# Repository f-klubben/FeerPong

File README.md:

# FeerPong
F-klubbens overengineered og goldplated beerpong table!

For quite a while, two beautifully painted tables have been sitting in the dark corners of jægerstuen, ready to be turned into the nerdiest (and therefore also, coolest) beer pong tables known to man. This repository has therefore been created to conquer this stalemate and bring the dream to life. Currently, it is a bit empty in here, but in the future, we will collect everything relating to the FeerPong table in here. This will include, but not limited to, 2D files for the laser cutter that will engrave the table (already [here](PhysicalDesign/2DLogoLaserCutting), whoop!), code to the ontable-hardware and, of course, documentation for it all.

## FeerPong ideas:
- F-klubbens logo encompassing the beers ingraved into the tables via laser cutting
  - See [the 2D logo laser cutting files](PhysicalDesign/2DLogoLaserCutting)
- Diodes, sensors and ontable-hardware that can be used for various extensions of the traditional beer pong, truly bringing forth the era of FeerPong
  - Protocol ideas: (You are welcome to add more!)
    - Under_Score_Protocol
      - All active cups (cups on the table that has not yet been consumed) light up 
    - Holy_Grail_Protocol:
      - Randomly an active cup will light up for a set time. If that cup is hit the team owning the cup, recieve a penalty (drink an extra beer/shot, they also have to drink adjecent cups, End_Case_Protocol/Recursive_Protocol starts for them etc.)
    - Counter_Attack_Protocol:
      - When a cup is taken away (because the opposite team hit it) one or more cups on the opposite side light up for a short time. If the team downs the beer and then hit one of the cups, the oppsite team recieves a penalty (drink an extra beer/shot, they also have to drink adjecent cups, End_Case_Protocol/Recursive_Protocol starts for them etc.)
    - End_Case_Protocol/Recursive_Protocol:
      - When a cup is taken away (because the opposite team hit it) a timer starts. When the timer runs out a cup light up and if the team  haven't downed their beer before that, they have to drink that beer too, starting a new timer (this continues until you down a beer before the timer runs out or loose the game). The timer could be customisable 
  - Crazy new ideas: (Again, add more!)
    - Account creation and cross-game score keeping
    - App/web-app integration for game control, account management etc.

(You are also welcome to correct any spelling mistakes you find)

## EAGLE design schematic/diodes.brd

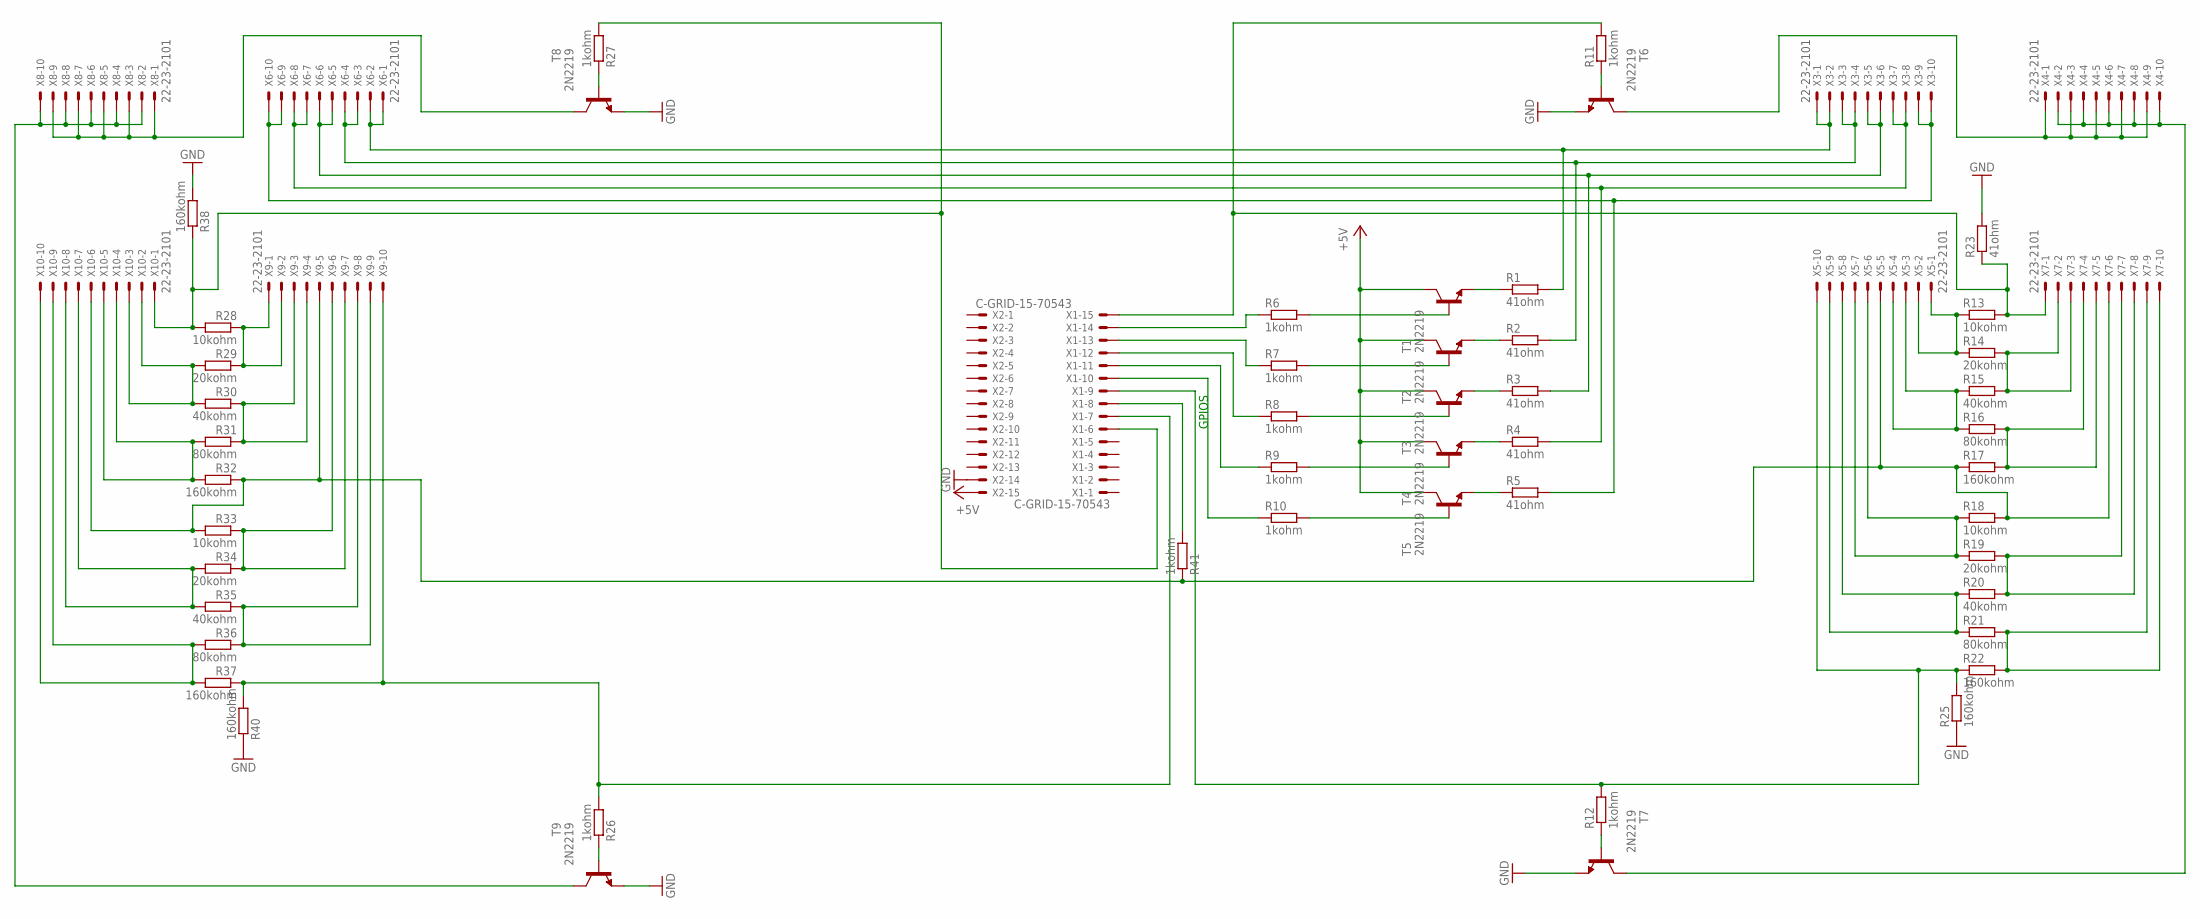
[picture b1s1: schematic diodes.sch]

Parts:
R1, R2, R3, R4, R5, R23: 41ohm; 0207/10
R6, R7, R8, R9, R10, R11, R12, R26, R27, R41: 1kohm; 0207/10
R13, R18, R28, R33: 10kohm; 0207/10
R14, R19, R29, R34: 20kohm; 0207/10
R15, R20, R30, R35: 40kohm; 0207/10
R16, R21, R31, R36: 80kohm; 0207/10
R17, R22, R25, R32, R37, R38, R40: 160kohm; 0207/10
T1, T2, T3, T4, T5, T6, T7, T8, T9: 2N2219; TO5
X1, X2: C-GRID-15-70543; 70543-15
X3, X4, X5, X6, X7, X8, X9, X10: 22-23-2101

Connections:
+5V: T1.3 (C), T2.3 (C), T3.3 (C), T4.3 (C), T5.3 (C), X2.15
GND: R23.2, R25.1, R38.2, R40.1, T6.1 (E), T7.1 (E), T8.1 (E), T9.1 (E), X2.14
unnamed: R6.2, T1.2 (B)
unnamed: R27.2, R28.2, R38.1, X1.6, X10.1
unnamed: T6.3 (C), X4.1, X4.3, X4.5, X4.7, X4.9
unnamed: R13.1, R14.1, X5.1, X5.2
unnamed: R41.2, X1.8
unnamed: R15.1, R16.1, X5.3, X5.4
unnamed: R3.1, T3.1 (E)
unnamed: R4.1, T4.1 (E)
unnamed: R5.1, T5.1 (E)
unnamed: R2.1, T2.1 (E)
unnamed: R1.1, T1.1 (E)
unnamed: R6.1, X1.14
unnamed: R7.1, X1.13
unnamed: R8.1, X1.12
unnamed: R9.1, X1.11
unnamed: R10.1, X1.10
unnamed: R10.2, T5.2 (B)
unnamed: R9.2, T4.2 (B)
unnamed: R8.2, T3.2 (B)
unnamed: R7.2, T2.2 (B)
unnamed: R14.2, R15.2, X7.2, X7.3
unnamed: R12.1, T7.2 (B)
unnamed: R11.1, T6.2 (B)
unnamed: R17.1, R18.2, R32.1, R33.2, R41.1, X5.5, X7.6, X9.5, X10.6
unnamed: R19.2, R20.2, X7.7, X7.8
unnamed: R21.2, R22.2, X7.9, X7.10
unnamed: R26.1, T9.2 (B)
unnamed: R27.1, T8.2 (B)
unnamed: T9.3 (C), X8.2, X8.4, X8.6, X8.8, X8.10
unnamed: R16.2, R17.2, X7.4, X7.5
unnamed: R33.1, R34.1, X9.6, X9.7
unnamed: R18.1, R19.1, X5.6, X5.7
unnamed: R2.2, X3.3, X3.4, X6.3, X6.4
unnamed: R1.2, X3.1, X3.2, X6.1, X6.2
unnamed: T7.3 (C), X4.2, X4.4, X4.6, X4.8, X4.10
unnamed: R20.1, R21.1, X5.8, X5.9
unnamed: R11.2, R13.2, R23.1, X1.15, X7.1
unnamed: R3.2, X3.5, X3.6, X6.5, X6.6
unnamed: R4.2, X3.7, X3.8, X6.7, X6.8
unnamed: R5.2, X3.9, X3.10, X6.9, X6.10
unnamed: R12.2, R22.1, R25.2, X1.9, X5.10
unnamed: T8.3 (C), X8.1, X8.3, X8.5, X8.7, X8.9
unnamed: R28.1, R29.1, X9.1, X9.2
unnamed: R30.1, R31.1, X9.3, X9.4
unnamed: R34.2, R35.2, X10.7, X10.8
unnamed: R35.1, R36.1, X9.8, X9.9
unnamed: R29.2, R30.2, X10.2, X10.3
unnamed: R31.2, R32.2, X10.4, X10.5
unnamed: R26.2, R37.1, R40.2, X1.7, X9.10
unnamed: R36.2, R37.2, X10.9, X10.10

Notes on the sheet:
GPIOS

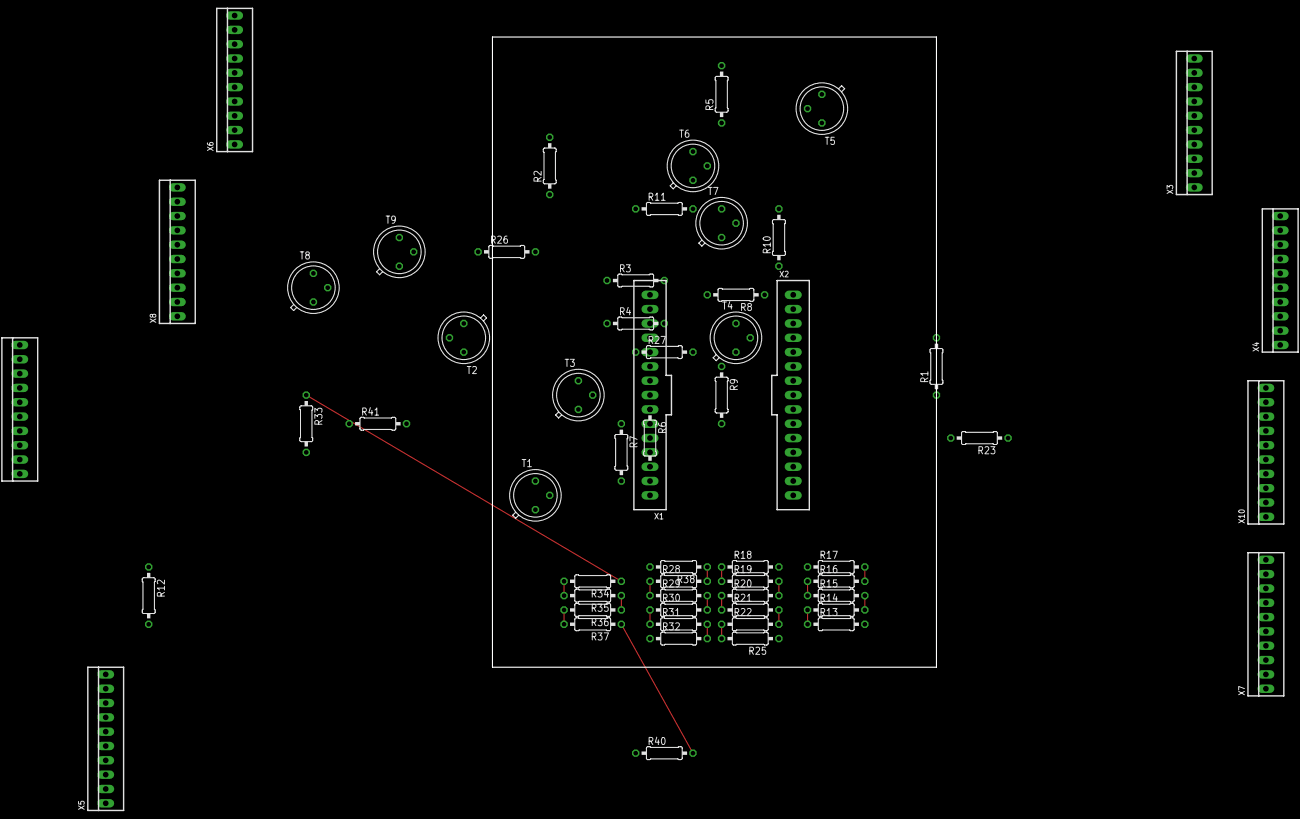
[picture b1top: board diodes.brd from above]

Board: 2 copper layers, 78.7 x 111.8 mm, 58 parts (0 on the bottom side), 52 nets.

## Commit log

2017-11-06 2D lasecutting files added
2017-11-15 Cleaned the laser cutting project file structure
2017-11-15 New and better names for laser cutter files
2017-11-15 Added initial schematic for hardware
2017-11-17 New hardware chip added to replace the Raspberry PI in the schematic
2018-04-06 init code
2018-04-06 Updated LED logic to include gnd PWM
2018-04-08 hacks
2018-04-10 Plack design and laser cutting design cleanup
2018-04-10 Updated file format for plack design
2018-04-10 Updated plack and original 89 logo
2018-04-10 General folder cleanup in Physical Design
2018-04-10 Updated plack pdf
2018-04-12 Fix invalid HTML
2018-04-12 init led schematic
2018-04-13 Updated diode schematic
2018-04-13 Flipped power direction on schematic
2018-04-13 Diode and button schematic updated with connectors
2018-04-13 Small changes and fix of PCB schematic
2018-04-15 Added dots to all 3+ junctions in the schematic and replaced ESP connector with a non-angled one
2018-04-15 Correct pin-placement for ESP on schematic and added board for printing
2018-04-15 Cleanup of unnessesary files in schematic folder
2018-04-15 Fixed all ERC warnings in schematic
2018-04-15 Updated board
2018-04-16 Updated board PCB
2023-10-26 Update gitignore and fix small issue with lib_compat_mode. Probably related to lib update
